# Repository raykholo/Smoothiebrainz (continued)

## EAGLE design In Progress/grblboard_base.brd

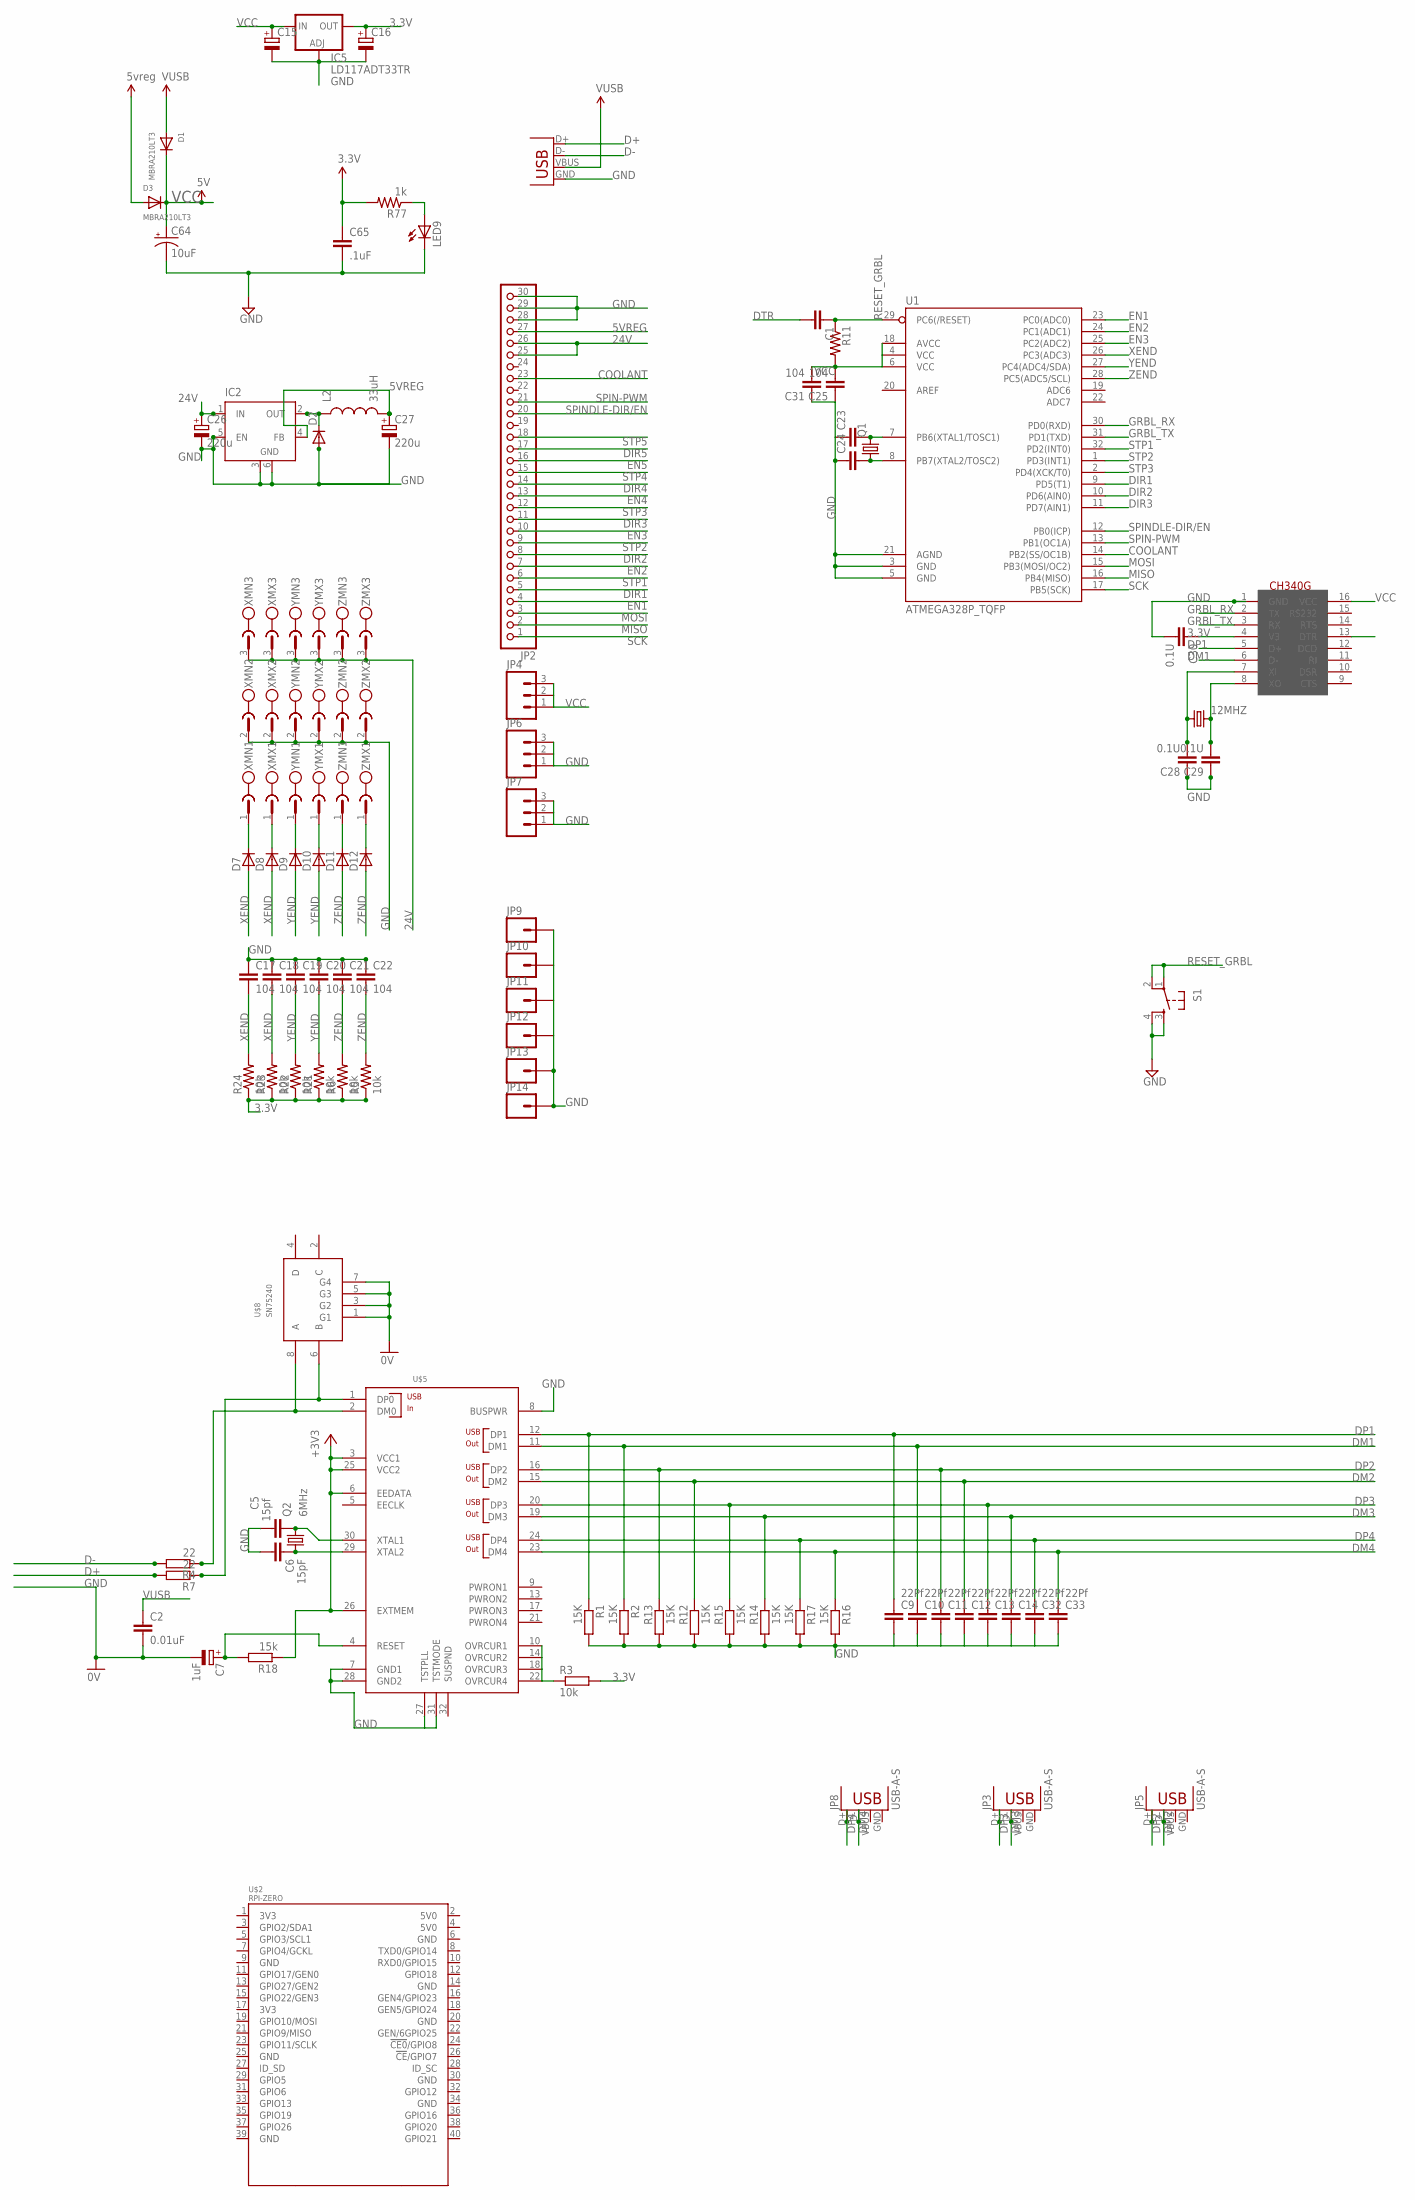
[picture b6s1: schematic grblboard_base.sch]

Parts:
12MHZ: CRYSTALHC49UP; HC49UP
C1, C23, C24: CAP1206; 1206
C2: 0.01uF; C0805
C5: 15pf; C0805
C6: 15pF; C0805
C7: 1uF; E2,5-6
C9, C10, C11, C12, C13, C14, C32, C33: 22Pf; C0805
C15, C16: CPOL-EUE2.5-7; E2,5-7
C17, C18, C19, C20, C21, C22: 104; C1206
C25, C31: 104; 1206
C26, C27: 220u; E2,5-7
C28, C29, C30: 0.1U; C1206
C64: 10uF; EIA3216
C65: .1uF; C0603
D1, D3: MBRA210LT3; SMADIODE
D2: DIODE-DO-214AC; DO-214AC
D7, D8, D9, D10, D11, D12: D-SOD-87; SOD87
IC2: LM2596S; TO263-5
IC5: LD117ADT33TR; DPACK
JP2: PINHD-1X30; 1X30
JP3, JP5, JP8: USB-A-S
JP4, JP6, JP7: M03POGO_PIN_HOLES_ONLY; 1X03_PP_HOLES_ONLY
JP9, JP10, JP11, JP12, JP13, JP14: M01NOSILK-KIT; 1X01NS-KIT
L2: 33uH; CDRH125
LED9: LEDCHIP-LED0805; CHIP-LED0805
Q1: CRYSTALHC49UP; HC49UP
Q2: 6MHz; HC49UP
R1, R2, R12, R13, R14, R15, R16, R17: 15K; R0805
R3: 10k; R0805
R4, R7: 22; R0805
R5, R6, R21, R22, R23, R24: 10k; M1206
R11: RESISTOR1206; 1206
R18: 15k; R0805
R77: 1k; R0603
S1: TAC_SWITCHSMD; TACTILE_SWITCH_SMD
U1: ATMEGA328P_TQFP; TQFP32-08
U$1: CH340G; SOIC16
U$2: RPI-ZERO; RASPBERRYPI_BASTELSTUBE_V13_RASPI_BOARD_B+_FULL
U$5: TUSB2046; LQFP-32
U$8: SN75240; TSSOP8
X14: USBPTH; USB-B-PTH
XMN: MC1.5/3; MC1.5/3-G-3.81
XMX: MC1.5/3; MC1.5/3-G-3.81
YMN: MC1.5/3; MC1.5/3-G-3.81
YMX: MC1.5/3; MC1.5/3-G-3.81
ZMN: MC1.5/3; MC1.5/3-G-3.81
ZMX: MC1.5/3; MC1.5/3-G-3.81

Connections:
3.3V: C16.+, C30.1, C65.1, IC5.4 (OUT), R3.2, R5.1, R6.1, R18.1, R21.1, R22.1, R23.1, R24.1, R77.2, U$1.4 (V3), U$5.3 (VCC1), U$5.6 (EEDATA), U$5.25 (VCC2), U$5.26 (EXTMEM)
5VREG: C27.+, D3.A, IC2.4 (FB), JP2.27, L2.2
24V: C26.+, IC2.1 (IN), JP2.25, JP2.26, XMN.3, XMX.3, YMN.3, YMX.3, ZMN.3, ZMX.3
COOLANT: JP2.23, U1.14 (PB2(SS/OC1B))
D+: R7.2, X14.D+
D-: R4.2, X14.D-
DIR1: JP2.5, U1.9 (PD5(T1))
DIR2: JP2.8, U1.10 (PD6(AIN0))
DIR3: JP2.11, U1.11 (PD7(AIN1))
DIR4: JP2.14
DIR5: JP2.17
DM0: R4.1, U$5.2 (DM0), U$8.8 (A)
DM1: C10.1, R2.1, U$1.6 (D-), U$5.11 (DM1)
DM2: C12.1, JP5.D-, R12.1, U$5.15 (DM2)
DM3: C14.1, JP3.D-, R14.1, U$5.19 (DM3)
DM4: C33.1, JP8.D-, R16.1, U$5.23 (DM4)
DP0: R7.1, U$5.1 (DP0), U$8.6 (B)
DP1: C9.1, R1.1, U$1.5 (D+), U$5.12 (DP1)
DP2: C11.1, JP5.D+, R13.1, U$5.16 (DP2)
DP3: C13.1, JP3.D+, R15.1, U$5.20 (DP3)
DP4: C32.1, JP8.D+, R17.1, U$5.24 (DP4)
DTR: C1.2, U$1.13 (DTR)
EN1: JP2.4, U1.23 (PC0(ADC0))
EN2: JP2.7, U1.24 (PC1(ADC1))
EN3: JP2.10, U1.25 (PC2(ADC2))
EN4: JP2.13
EN5: JP2.16
GND: C2.2, C5.1, C6.2, C7.-, C9.2, C10.2, C11.2, C12.2, C13.2, C14.2, C15.-, C16.-, C17.1, C18.1, C19.1, C20.1, C21.1, C22.1, C23.1, C24.1, C25.1, C26.-, C27.-, C28.1, C29.1, C30.2, C31.1, C32.2, C33.2, C64.C (-), C65.2, D2.2 (A), IC2.3 (GND), IC2.5 (EN), IC2.6 (GND), IC5.1 (ADJ), JP2.28, JP2.29, JP2.30, JP6.1, JP6.2, JP6.3, JP7.1, JP7.2, JP7.3, JP9.1, JP10.1, JP11.1, JP12.1, JP13.1, JP14.1, LED9.C, R1.2, R2.2, R12.2, R13.2, R14.2, R15.2, R16.2, R17.2, S1.3, S1.4, U1.3 (GND), U1.5 (GND), U1.21 (AGND), U$1.1 (GND), U$5.7 (GND1), U$5.8 (BUSPWR), U$5.27 (TSTPLL), U$5.28 (GND2), U$5.31 (TSTMODE), U$8.1 (G1), U$8.3 (G2), U$8.5 (G3), U$8.7 (G4), X14.GND, XMN.2, XMX.2, YMN.2, YMX.2, ZMN.2, ZMX.2
GRBL_RX: U1.30 (PD0(RXD)), U$1.2 (TX)
GRBL_TX: U1.31 (PD1(TXD)), U$1.3 (RX)
MISO: JP2.2, U1.16 (PB4(MISO))
MOSI: JP2.3, U1.15 (PB3(MOSI/OC2))
unnamed: R3.1, U$5.10 (OVRCUR1), U$5.14 (OVRCUR2), U$5.18 (OVRCUR3), U$5.22 (OVRCUR4)
unnamed: 12MHZ.1, C28.2, U$1.7 (XI)
unnamed: D7.1 (C), XMN.1
unnamed: D8.1 (C), XMX.1
unnamed: D2.1 (C), IC2.2 (OUT), L2.1
unnamed: D9.1 (C), YMN.1
unnamed: D10.1 (C), YMX.1
unnamed: C23.2, Q1.2, U1.7 (PB6(XTAL1/TOSC1))
unnamed: C24.2, Q1.1, U1.8 (PB7(XTAL2/TOSC2))
unnamed: D11.1 (C), ZMN.1
unnamed: D12.1 (C), ZMX.1
unnamed: 12MHZ.2, C29.2, U$1.8 (XO)
unnamed: LED9.A, R77.1
RESET: C7.+, R18.2, U$5.4 (RESET)
RESET_GRBL: C1.1, R11.1, S1.1, S1.2, U1.29 (PC6(/RESET))
SCK: JP2.1, U1.17 (PB5(SCK))
SPIN-PWM: JP2.21, U1.13 (PB1(OC1A))
SPINDLE-DIR/EN: JP2.20, U1.12 (PB0(ICP))
STP1: JP2.6, U1.32 (PD2(INT0))
STP2: JP2.9, U1.1 (PD3(INT1))
STP3: JP2.12, U1.2 (PD4(XCK/T0))
STP4: JP2.15
STP5: JP2.18
VCC: C15.+, C25.2, C31.2, C64.A (+), D1.C, D3.C, IC5.3 (IN), JP4.1, JP4.2, JP4.3, R11.2, U1.4 (VCC), U1.6 (VCC), U1.18 (AVCC), U$1.16 (VCC)
VUSB: C2.1, D1.A, X14.VBUS
XEND: C17.2, C18.2, D7.2 (A), D8.2 (A), R23.2, R24.2, U1.26 (PC3(ADC3))
XTAL1: C5.2, Q2.2, U$5.30 (XTAL1)
XTAL2: C6.1, Q2.1, U$5.29 (XTAL2)
YEND: C19.2, C20.2, D9.2 (A), D10.2 (A), R21.2, R22.2, U1.27 (PC4(ADC4/SDA))
ZEND: C21.2, C22.2, D11.2 (A), D12.2 (A), R5.2, R6.2, U1.28 (PC5(ADC5/SCL))

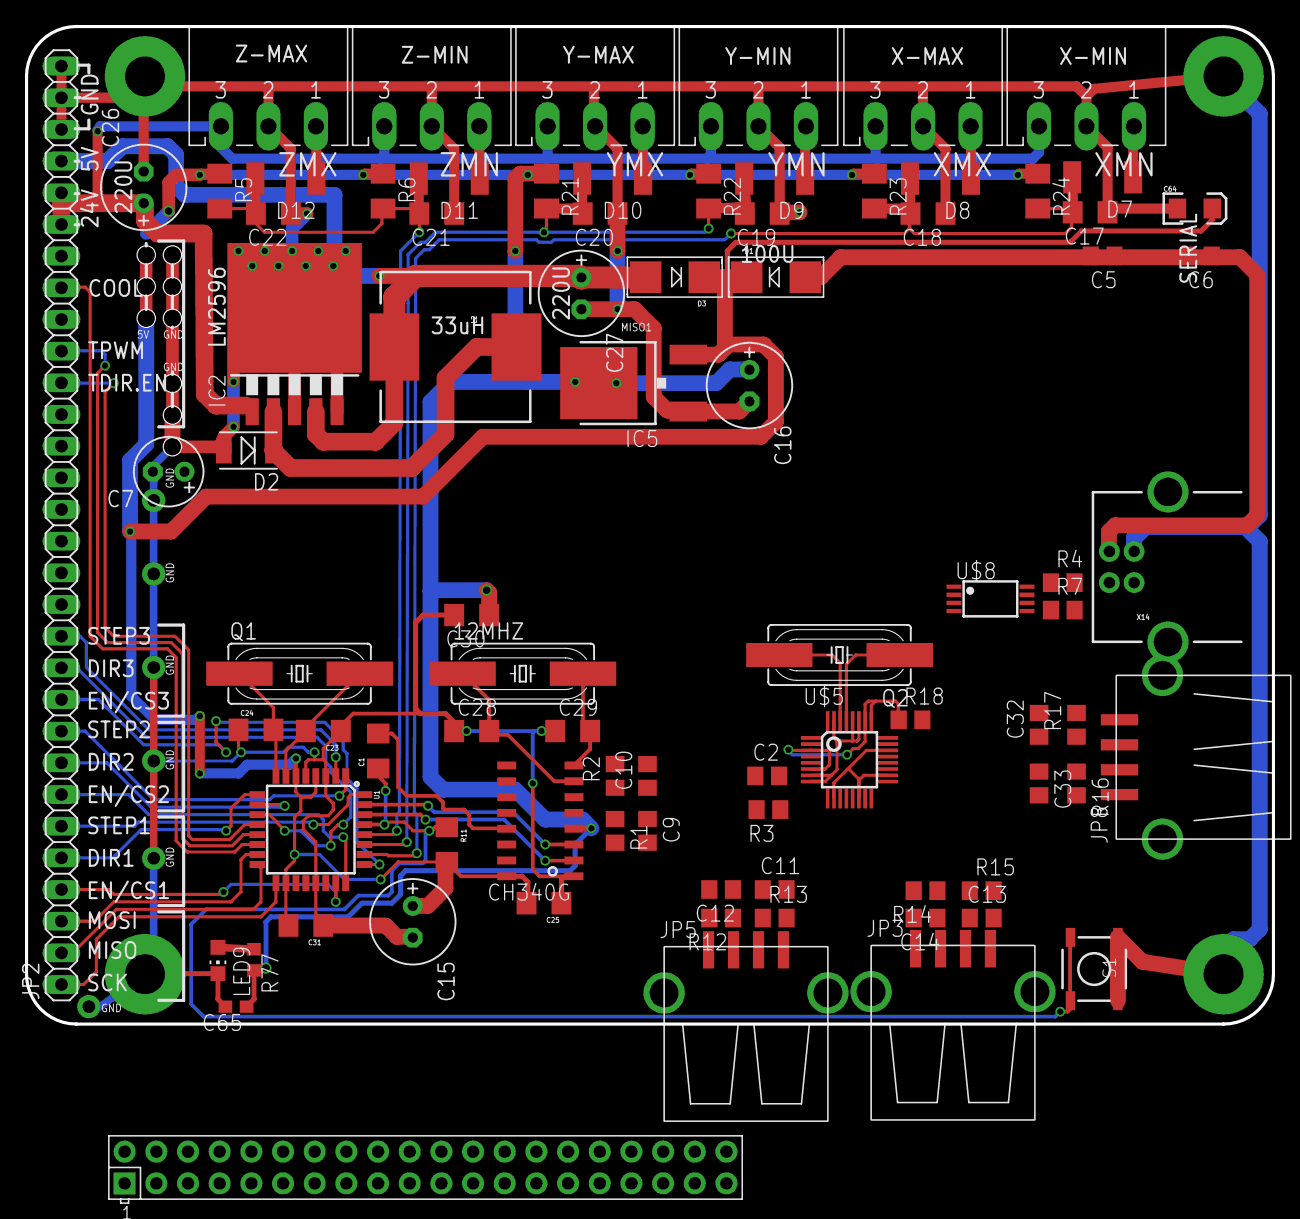
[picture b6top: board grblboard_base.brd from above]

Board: 2 copper layers, 100.0 x 80.0 mm, 94 parts (0 on the bottom side), 56 nets.

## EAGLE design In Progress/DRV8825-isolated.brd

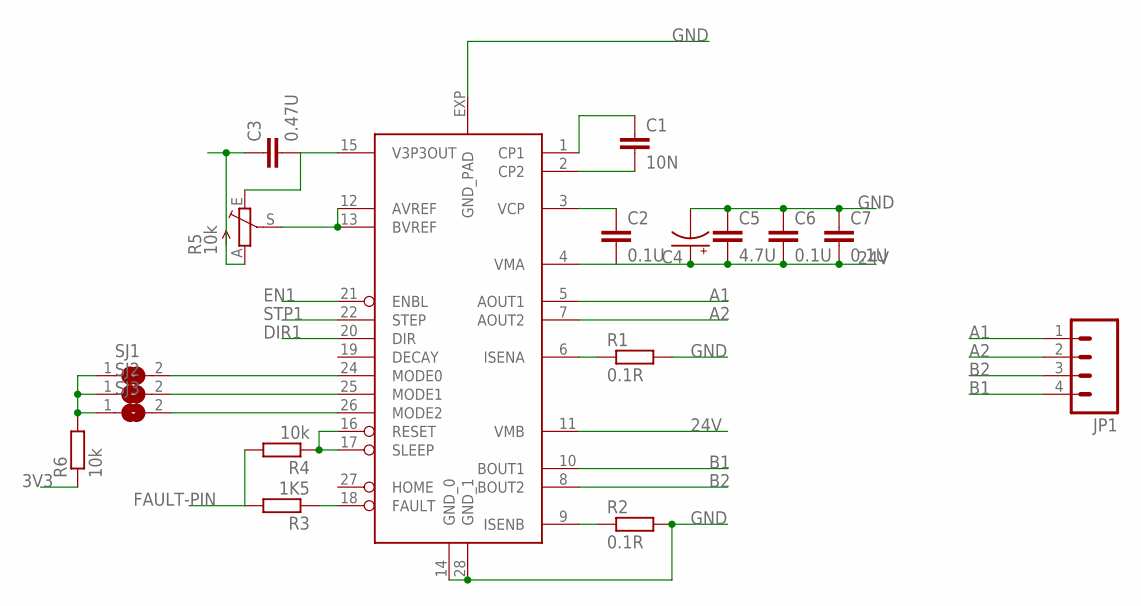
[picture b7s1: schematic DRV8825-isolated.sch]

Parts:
C1: 10N; 1206
C2, C6, C7: 0.1U; 1206
C3: 0.47U; 1206
C4: CPOL-USE2.5-7; E2,5-7
C5: 4.7U; 1206
JP1: M04SCREW; SCREWTERMINAL-3.5MM-4
R1, R2: 0.1R; R1206
R3: 1K5; M1206
R4: 10k; M1206
R5: 10k; S64W
R6: 10k; R1206
SJ1, SJ2, SJ3: SJ
U$1: DRV8825PWP; TSSOP-28

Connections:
3V3: R6.1
24V: C2.2, C4.+, C5.2, C6.2, C7.2, U$1.4 (VMA), U$1.11 (VMB)
A1: JP1.1, U$1.5 (AOUT1)
A2: JP1.2, U$1.7 (AOUT2)
B1: JP1.4, U$1.10 (BOUT1)
B2: JP1.3, U$1.8 (BOUT2)
CP1: C1.1, U$1.1 (CP1)
CP2: C1.2, U$1.2 (CP2)
DIR1: U$1.20 (DIR)
EN1: U$1.21 (ENBL)
FAULT: R3.1, U$1.18 (FAULT)
FAULT-PIN: R3.2, R4.2
GND: C3.1, C4.-, C5.1, C6.1, C7.1, R1.2, R2.2, R5.A, U$1.14 (GND_0), U$1.28 (GND_1), U$1.EXP (GND_PAD)
MSPULLUP: R6.2, SJ1.1, SJ1.2, SJ2.1, SJ2.2, SJ3.1, SJ3.2, U$1.24 (MODE0), U$1.25 (MODE1), U$1.26 (MODE2)
unnamed: R5.S, U$1.12 (AVREF), U$1.13 (BVREF)
SENA: R1.1, U$1.6 (ISENA)
SENB: R2.1, U$1.9 (ISENB)
SLEEP: R4.1, U$1.16 (RESET), U$1.17 (SLEEP)
STP1: U$1.22 (STEP)
V3VP: C3.2, R5.E, U$1.15 (V3P3OUT)
VCP: C2.1, U$1.3 (VCP)

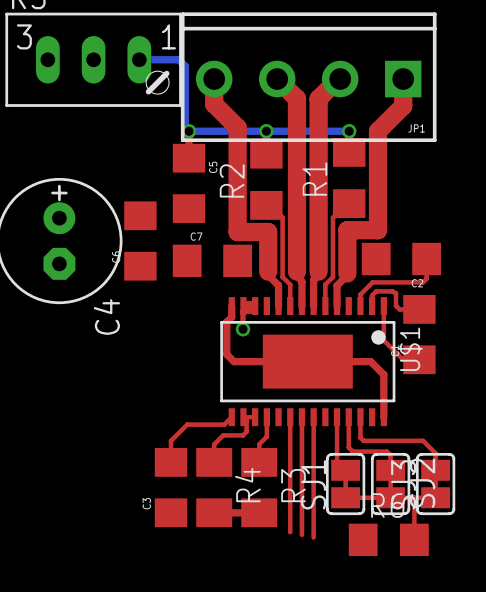
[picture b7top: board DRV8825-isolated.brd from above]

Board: 2 copper layers, 18 parts (0 on the bottom side), 17 nets.

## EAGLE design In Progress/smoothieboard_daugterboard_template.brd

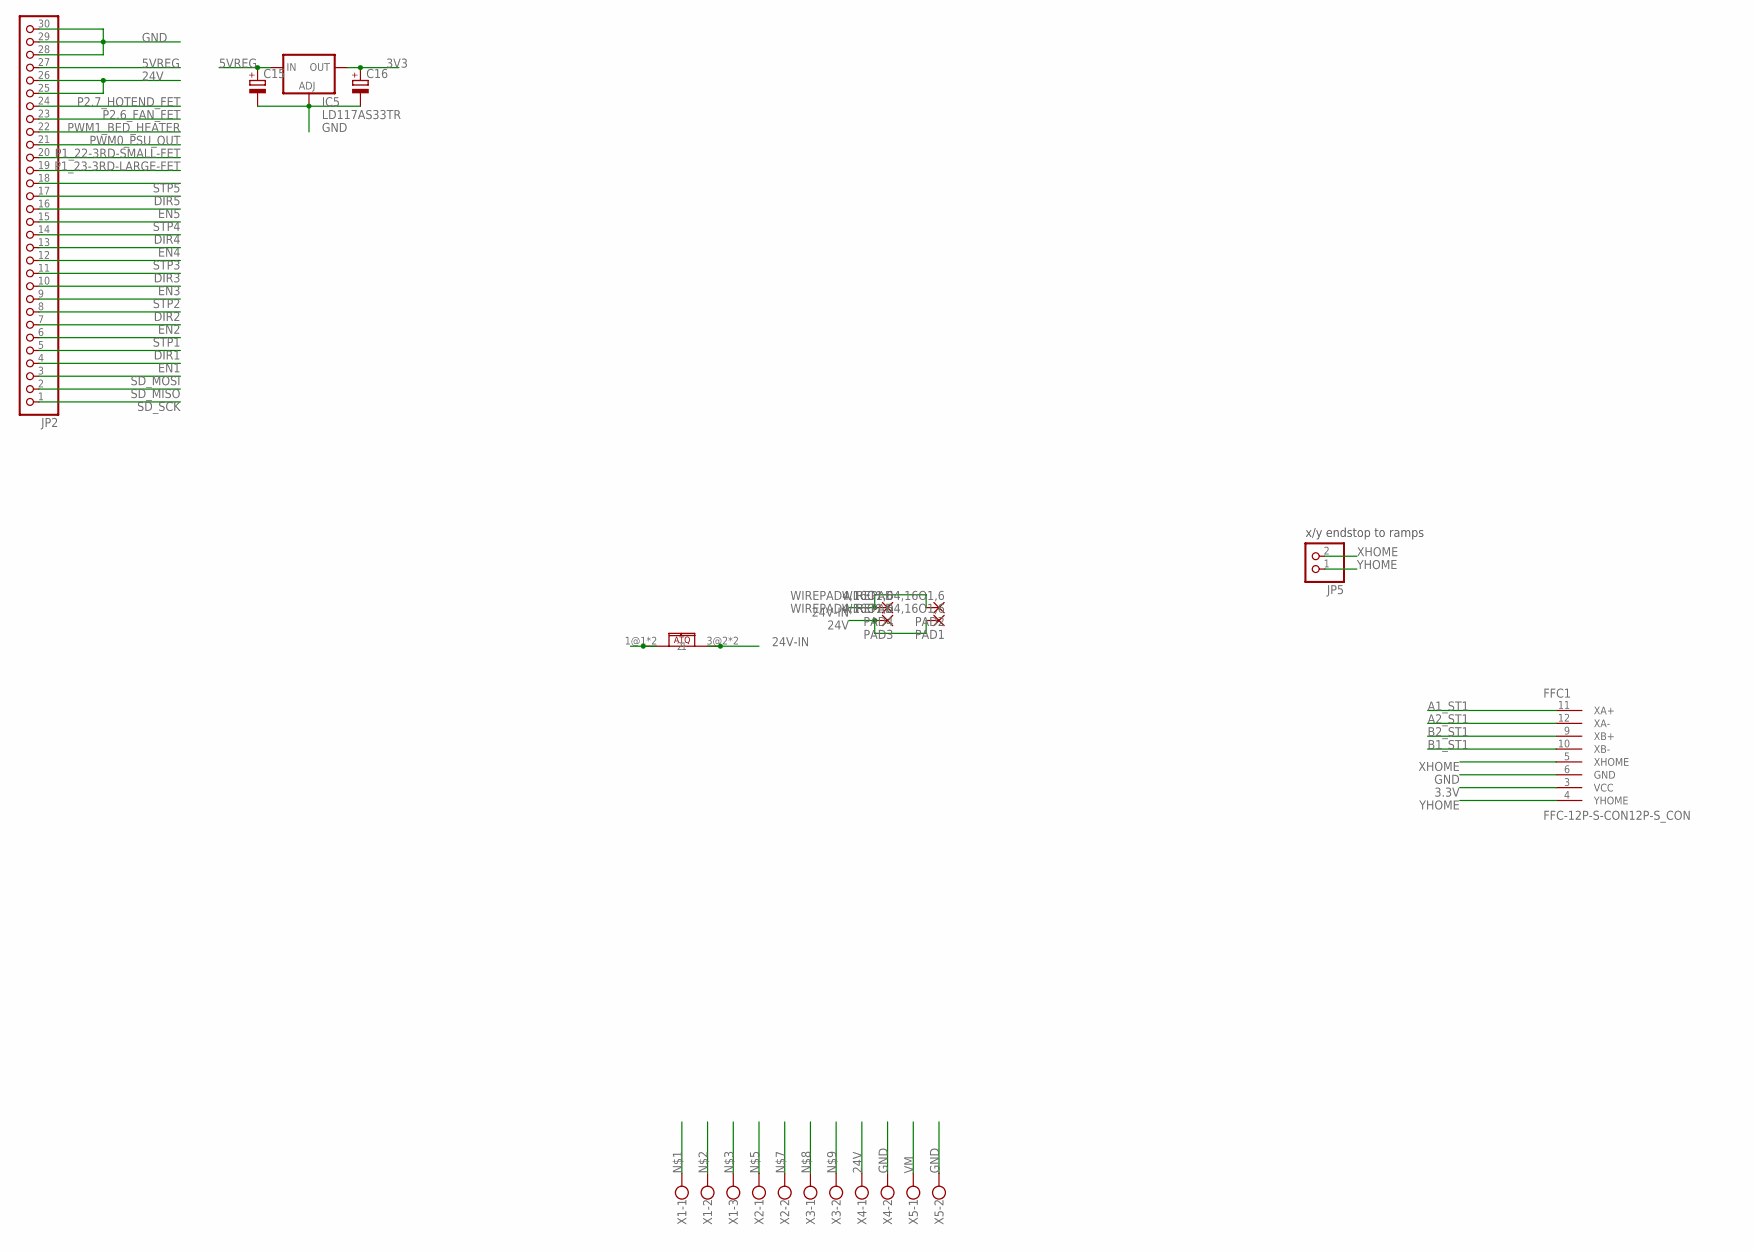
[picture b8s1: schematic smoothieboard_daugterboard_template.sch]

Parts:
C15: CPOL-EUE2.5-7; E2,5-7
C16: CPOL-EUE2.5-6; E2,5-6
FFC1: FFC-12P-S-CON12P-S_CON; FFC
IC5: LD117AS33TR; SOT223
JP2: PINHD-1X30; 1X30
JP5: PINHD-1X2; 1X02
PAD1, PAD2, PAD3, PAD4: WIREPAD4,16O1,6; 4,16O1,6
U$7: CQ-121; CQ121
X1: W237-103
X2, X3, X4, X5: W237-102

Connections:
3.3V: FFC1.3 (VCC)
3V3: C16.+, IC5.4 (OUT)
5VREG: C15.+, IC5.3 (IN), JP2.27
24V: JP2.25, JP2.26, PAD1.1, PAD3.1, X4.1
24V-IN: PAD2.1, PAD4.1, U$7.3@2 (2), U$7.4@2 (2)
A1_ST1: FFC1.11 (XA+)
A2_ST1: FFC1.12 (XA-)
B1_ST1: FFC1.10 (XB-)
B2_ST1: FFC1.9 (XB+)
DIR1: JP2.5
DIR2: JP2.8
DIR3: JP2.11
DIR4: JP2.14
DIR5: JP2.17
EN1: JP2.4
EN2: JP2.7
EN3: JP2.10
EN4: JP2.13
EN5: JP2.16
GND: C15.-, C16.-, FFC1.6 (GND), IC5.1 (ADJ), JP2.28, JP2.29, JP2.30, X4.2, X5.2
P1_22-3RD-SMALL-FET: JP2.20
P1_23-3RD-LARGE-FET: JP2.19
P2.6_FAN_FET: JP2.23
P2.7_HOTEND_FET: JP2.24
PWM0_PSU_OUT: JP2.21
PWM1_BED_HEATER: JP2.22
SD_MISO: JP2.2
SD_MOSI: JP2.3
SD_SCK: JP2.1
STP1: JP2.6
STP2: JP2.9
STP3: JP2.12
STP4: JP2.15
STP5: JP2.18
VM: U$7.1@1 (1), U$7.2@1 (1), X5.1
XHOME: FFC1.5 (XHOME), JP5.2
YHOME: FFC1.4 (YHOME), JP5.1

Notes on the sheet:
x/y endstop to ramps

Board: 2 copper layers, 16 parts (0 on the bottom side), 8 nets, no tracks yet.

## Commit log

2016-04-01 Smoothiebrainz V2
2016-04-01 Updated TODO
2016-04-01 Updated todo: Fiducials
2016-04-02 Standardized board to all 0603 components.
    Also added some headers to schematic and cleaned up brd. Consider
    changing C67 (the only 1UF cap, used as power filter on the SD circuit)
    to 10uF which is already on the BOM.
2016-04-02 Minor routing cleanup
2016-04-03 Teardown, Added Stepper Drivers, X Motor Traces Type 1
2016-04-03 Motor 1 Solder Jumpers on Bottom Layer
2016-04-03 More trace ripup. About to change motor 1 traces
2016-04-03 New Motor1 Traces
2016-04-04 2 templates for stepper driver completed
2016-04-04 About to change 24v rail
2016-04-05 Lots of voltage rails and pours
2016-04-05 heatbed mosfet/ motor driver changes
2016-04-06 need to remove signal connector from Y stepper
2016-04-06 about to revert y stepper layout
2016-04-06 3rd motor wired
2016-04-06 fun with autorouter 1
2016-04-06 revert autorouter
2016-04-07 Save Often
2016-04-08 lan8720 routed, added mosfets
2016-04-08 heater 1 circuit, lots of copper pours
2016-04-10 All Endstops wired. About to remove jtag.
2016-04-10 Removed jtag and ripped up traces. About to remove LAN8720.
    Going to (eventually) replace LAN8720 expansion module with direct
    onboard ethernet like Smoothieboard.
2016-04-10 Removed Lan8720
2016-04-10 Moved 6 x Endstops row.
2016-04-10 Moved 3 x Thermistors. About to ripup rest.
2016-04-10 Moved endstops to bottom right half of board.
2016-04-10 Moved a few passives, time to play with autorouter.
2016-04-10 Look what the autorouter "suggested". Meh.
2016-04-11 All 4 Normal MOSFETS Wired
2016-04-11 Forgot a polygon for mosfet 4. Added it now.
2016-04-11 About to relocate 5v output
2016-04-11 Potential placement of LCD jacks
2016-04-11 LCD Jacks back to normal
2016-04-12 About to ripup lcd traces
2016-04-13 partial motor routing, better ground for stepstick sockets
2016-04-13 First 4 motor traces routed
2016-04-13 Changed 1uF Capacitor near SD card to 10uf
2016-04-14 added onboard Ethernet, now need to reposition LEDS and 3v3 reg
2016-04-14 need to try movingover to 7.62mm connectors
2016-04-15 switched to 7.62mm power terminals
2016-04-15 replaced power conn with 7.62mm blocks, fixed heatbed mosfet pours
2016-04-15 Cleanup, first public preview.
2016-04-15 added flyback diodes to mosfets, re-routed 5v bus to endstops. About to remove ethernet
2016-04-15 Removed ethernet, put ESP8266 in its place
2016-04-15 passives for ESP8266 moved in
2016-04-15 about to remove bt
2016-04-16 Initial thermistor placement
2016-04-16 thermistor circuit, needs to be redone. big time.
2016-04-16 endstop power routing variant 1
2016-04-16 lots of motor routing complete
2016-04-16 removed old thermistors
2016-04-17 ran autorouter for research purposes
2016-04-17 reverted from auto
2016-04-17 mosfet #6 added to board
2016-04-17 motor 5 routed
2016-04-17 mosfet6 circuit complete, lots more routing
2016-04-17 ran auto for some sanity
2016-04-17 Revert "ran auto for some sanity"
    This reverts commit 1ed6ee52647e90fc58e62b905c32a851aa249b6f.
2016-04-17 BOM-0
2016-04-18 routed motor 6, some lcd traces
2016-04-18 insufficient gnd for motors
2016-04-18 Major rework of Y motor driver layout and increased gnd planes
2016-04-20 major routing complete
2016-04-20 more routing, almost done
2016-04-21 Finished routing, cleanup, and DRC processing.
    I just need to fix the 4 remaining motor drivers per the template
    already done on the first 2. Time for some community review.
2016-04-21 Servo connector added!
2016-04-21 added solder jumper to pcb thermistor circuit
2016-04-21 Routing cleaned up
2016-04-21 motor 3 re-routed
2016-04-21 motor 4 wires
2016-04-21 motor 5 wired
2016-04-21 motor 6 wired. Done routing.
2016-04-21 added 12v accessory header
2016-04-22 bottom silk
2016-04-22 Done.
2016-04-22 Just a few more tweaks
2016-04-22 Fixed all 45 degree DRC errors (that weren't under pads)
2016-04-22 Silk cleanup, gerbers generation
